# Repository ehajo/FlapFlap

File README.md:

# FlapFlap

Die Daten zum Fallblattanzeigen-Projekt, das wir auf Youtube und im Twitch-Livestream bearbeiten.

Unsere Streams findest du auf https://www.twitch.tv/ehajo

Die neue Version bekommt eine komplett neue Hardware. Es wird sowohl die komplette Ansteuerung als auch die Absolutpositionsabfrage getauscht!

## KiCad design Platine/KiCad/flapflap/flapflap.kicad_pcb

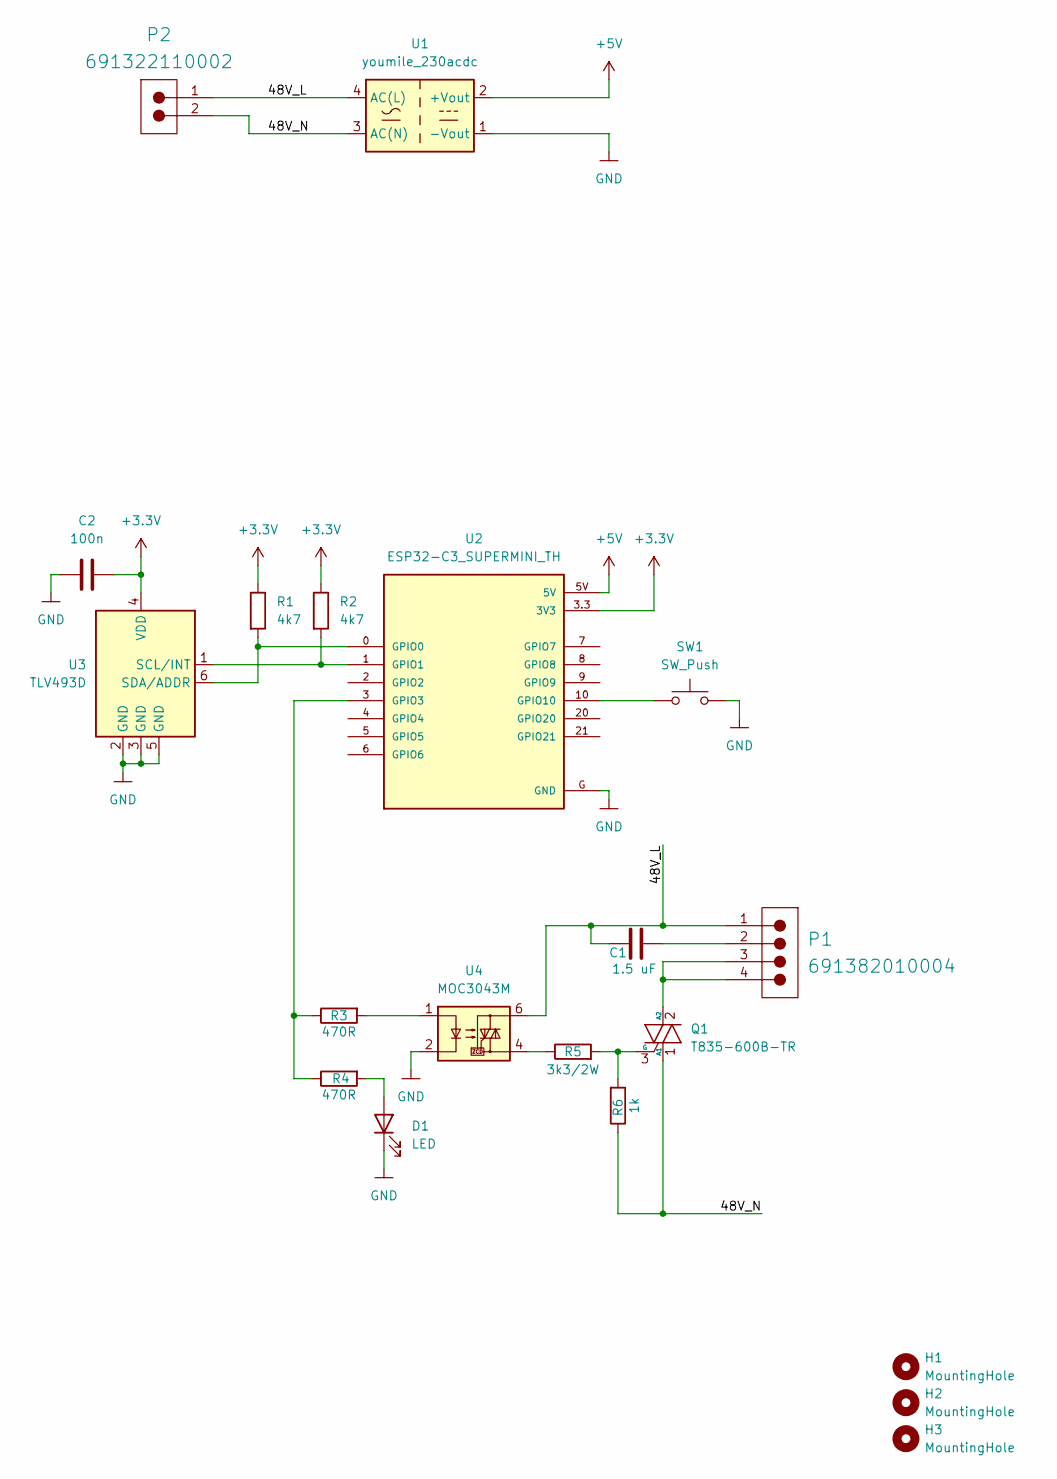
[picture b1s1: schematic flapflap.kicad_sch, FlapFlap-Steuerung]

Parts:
C1: 1.5 uF; C_Wurth_WCAP-FTBP-P22.5L26W7H16.5; Voltage 250; Part Number 890273326007CS
C2: 100n; C_0805_2012Metric_Pad1.18x1.45mm_HandSolder
D1: LED; LED_0805_2012Metric_Pad1.15x1.40mm_HandSolder
H1, H2, H3: MountingHole; MountingHole_3.2mm_M3
P1: 691382010004; 691382000004; Working Voltage 300V; Manufacturer Part Number 691382000004
P2: 691322110002; 691321300002; Working Voltage 300V; Manufacturer Part Number 691321300002
Q1: T835-600B-TR; TO-252-2
R1, R2: 4k7; R_0805_2012Metric_Pad1.20x1.40mm_HandSolder
R3, R4: 470R; R_0805_2012Metric_Pad1.20x1.40mm_HandSolder
R5: 3k3/2W; R_Axial_DIN0414_L11.9mm_D4.5mm_P15.24mm_Horizontal
R6: 1k; R_0805_2012Metric_Pad1.20x1.40mm_HandSolder
SW1: SW_Push; SW_SPST_FSMSM
U1: youmile_230acdc; ACDC-230
U2: ESP32-C3_SUPERMINI_TH; MODULE_ESP32-C3_SUPERMINI_TH
U3: TLV493D; SOT-23-6
U4: MOC3043M; DIP-6_W7.62mm_SMDSocket_SmallPads

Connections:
+3.3V: C2.2, R1.1, R2.1, U2.3.3 (3V3), U3.4 (VDD)
+5V: U1.2 (+Vout), U2.5V
/48V_L: C1.1, P1.1, P2.1, U1.4 (AC(L)), U4.6
/48V_N: P2.2, Q1.1 (A1), R6.1, U1.3 (AC(N))
GND: C2.1, D1.1 (K), SW1.1, U1.1 (-Vout), U2.G (GND), U3.2 (GND), U3.3 (GND), U3.5 (GND), U4.2
unnamed: C1.2, P1.2
unnamed: D1.2 (A), R4.2
unnamed: P1.3, P1.4, Q1.2 (A2)
unnamed: Q1.3 (G), R5.2, R6.2
unnamed: R3.2, U4.1
unnamed: R5.1, U4.4
unnamed: R1.2, U2.0 (GPIO0), U3.6 (SDA/ADDR)
unnamed: R2.2, U2.1 (GPIO1), U3.1 (SCL/INT)
unnamed: R3.1, R4.1, U2.3 (GPIO3)
unnamed: SW1.2, U2.10 (GPIO10)

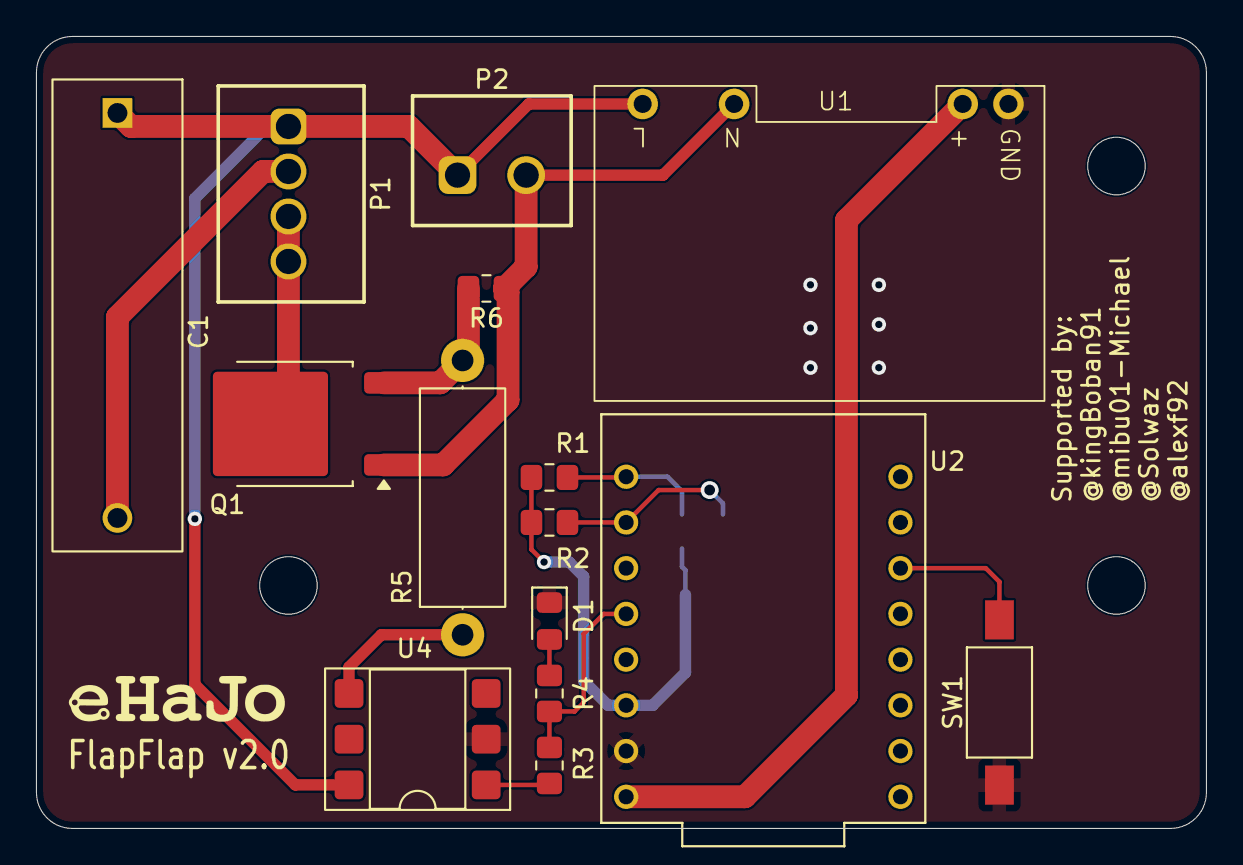
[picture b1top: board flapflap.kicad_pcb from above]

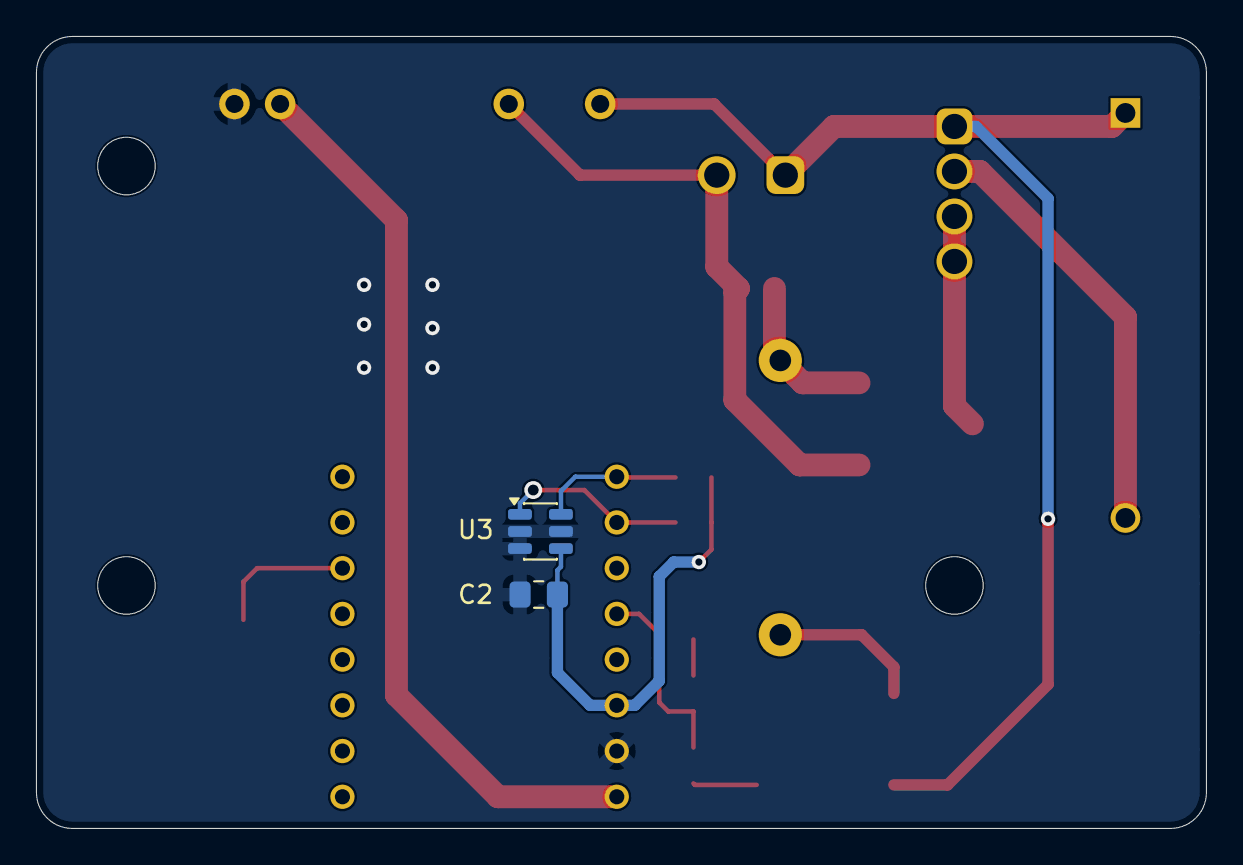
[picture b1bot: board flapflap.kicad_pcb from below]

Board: 2 copper layers, 65.0 x 44.0 mm, 20 parts (2 on the bottom side), 15 nets.

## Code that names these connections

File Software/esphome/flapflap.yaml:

esphome:
  name: flapflap-stunde
  on_boot:
    priority: -100
    then:
      - delay: 1s
      - lambda: |-
          id(tlv_test).set_pages((int) id(pages_number).state);
          id(tlv_test).set_zero_angle(id(zero_angle_number).state);
          id(tlv_test).set_calibration_leaf((int) id(calibration_leaf_number).state);
          id(tlv_test).set_target_leaf((int) id(target_leaf_number).state);
          id(tlv_test).set_mode("Stunden");

external_components:
  - source:
      type: local
      path: my_components

esp32:
  board: esp32-c3-devkitm-1
  framework:
    type: arduino

logger:
  level: DEBUG

api:
  encryption:
    key: "VgD8k05glNhFwXwStnMPbjwfET4pIDJ3TDBhezexu5A="

ota:
  - platform: esphome
    password: "1b5f8b66616918112e6f7647a8effe6e"

wifi:
  ssid: !secret wifi_ssid
  password: !secret wifi_password
  output_power: 8.5dB

time:
  - platform: sntp
    id: internet_time
    timezone: Europe/Berlin

i2c:
  sda: GPIO0
  scl: GPIO1
  scan: true
  frequency: 100kHz

binary_sensor:
  - platform: gpio
    id: flap_button
    name: "FlapFlap Taster"
    pin:
      number: GPIO10
      mode:
        input: true
        pullup: true
      inverted: true
    filters:
      - delayed_on: 20ms
      - delayed_off: 20ms
    on_press:
      then:
        - lambda: |-
            id(tlv_test).pulse_once();

button:
  - platform: restart
    name: "FlapFlap Neustart"

  - platform: template
    name: "FlapFlap Hier kalibrieren"
    on_press:
      then:
        - lambda: |-
            id(tlv_test).calibrate_here();
            auto call = id(zero_angle_number).make_call();
            call.set_value(id(tlv_test).get_zero_angle());
            call.perform();

  - platform: template
    name: "FlapFlap Sensor neu initialisieren"
    on_press:
      then:
        - lambda: |-
            id(tlv_test).reinitialize_sensor();

  - platform: template
    name: "FlapFlap Einzelpuls"
    on_press:
      then:
        - lambda: |-
            id(tlv_test).pulse_once();

  - platform: template
    name: "FlapFlap Ein Blatt weiter"
    on_press:
      then:
        - lambda: |-
            id(tlv_test).advance_one_leaf();

  - platform: template
    name: "FlapFlap Zu Zielblatt fahren"
    on_press:
      then:
        - lambda: |-
            id(tlv_test).start_move_to_target();

  - platform: template
    name: "FlapFlap Stop"
    on_press:
      then:
        - lambda: |-
            id(tlv_test).stop_move();

number:
  - platform: template
    name: "FlapFlap Nullwinkel"
    id: zero_angle_number
    min_value: 0
    max_value: 359.9
    step: 0.1
    optimistic: true
    restore_value: true
    initial_value: 0.0
    set_action:
      - lambda: |-
          id(tlv_test).set_zero_angle(x);

  - platform: template
    name: "FlapFlap Kalibrierblatt"
    id: calibration_leaf_number
    min_value: 0
    max_value: 61
    step: 1
    optimistic: true
    restore_value: true
    initial_value: 0
    set_action:
      - lambda: |-
          id(tlv_test).set_calibration_leaf((int) x);

  - platform: template
    name: "FlapFlap Zielblatt"
    id: target_leaf_number
    min_value: 0
    max_value: 61
    step: 1
    optimistic: true
    restore_value: true
    initial_value: 0
    set_action:
      - lambda: |-
          id(tlv_test).set_target_leaf((int) x);

  - platform: template
    name: "FlapFlap Blattanzahl"
    id: pages_number
    min_value: 1
    max_value: 100
    step: 1
    optimistic: true
    restore_value: true
    initial_value: 62
    set_action:
      - lambda: |-
          id(tlv_test).set_pages((int) x);

select:
  - platform: template
    name: "FlapFlap Modus"
    id: mode_select
    optimistic: true
    restore_value: false
    options:
      - Sekunden
      - Minuten
      - Stunden
      - Leerblatt
      - Kalibrierung
      - Manuell
    initial_option: Stunden
    set_action:
      - lambda: |-
          id(tlv_test).set_mode(x);

tlv493d_test:
  id: tlv_test
  update_interval: 20ms
  zero_angle: 0.0
  calibration_leaf: 0
  target_leaf: 0
  pages: 62
  mode: "Stunden"
  sensor_samples: 8
  motor_pin: GPIO3
  motor_pulse_ms: 30
  motor_settle_ms: 35
  move_timeout_ms: 15000
  max_pulses_per_move: 120
  unchanged_limit: 8
  move_stop_lead: 0.35
  seconds_stop_lead: 0.12

sensor:
  - platform: template
    name: "FlapFlap X"
    unit_of_measurement: "uT"
    accuracy_decimals: 1
    update_interval: 500ms
    lambda: |-
      return id(tlv_test).get_x_ut();

  - platform: template
    name: "FlapFlap Y"
    unit_of_measurement: "uT"
    accuracy_decimals: 1
    update_interval: 500ms
    lambda: |-
      return id(tlv_test).get_y_ut();

  - platform: template
    name: "FlapFlap Z"
    unit_of_measurement: "uT"
    accuracy_decimals: 1
    update_interval: 500ms
    lambda: |-
      return id(tlv_test).get_z_ut();

  - platform: template
    name: "FlapFlap Winkel"
    unit_of_measurement: "°"
    accuracy_decimals: 1
    update_interval: 500ms
    lambda: |-
      return id(tlv_test).get_angle_deg();

  - platform: template
    name: "FlapFlap Aktuelles Blatt"
    accuracy_decimals: 0
    update_interval: 250ms
    lambda: |-
      return id(tlv_test).get_current_leaf();

  - platform: template
    name: "FlapFlap Zielblatt aktiv"
    accuracy_decimals: 0
    update_interval: 250ms
    lambda: |-
      return id(tlv_test).get_target_leaf();

  - platform: template
    name: "FlapFlap Aktiver Nullwinkel"
    unit_of_measurement: "°"
    accuracy_decimals: 1
    update_interval: 1s
    lambda: |-
      return id(tlv_test).get_zero_angle();

  - platform: template
    name: "FlapFlap Pulse im aktuellen Lauf"
    accuracy_decimals: 0
    update_interval: 250ms
    lambda: |-
      return id(tlv_test).get_move_pulses();

text_sensor:
  - platform: template
    name: "FlapFlap Status"
    update_interval: 250ms
    lambda: |-
      return {id(tlv_test).get_status_text()};

interval:
  - interval: 1s
    then:
      - lambda: |-
          auto now = id(internet_time).now();
          if (now.is_valid()) {
            id(tlv_test).update_clock_time(now.hour, now.minute, now.second);
          }

  - interval: 10s
    then:
      - lambda: |-
          ESP_LOGD("main", "FlapFlap aktiv: I2C GPIO0/1, Taster GPIO10, MOC GPIO3");

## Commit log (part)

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2018-03-20 :boom::camel: Added .gitattributes & .gitignore files
2018-03-20 Initial commit
    Erste Version
2024-09-28 Sortiert in neuen Ordner
    Weg frei für die neue Version!
2024-10-02 CAD update
    jetzt sogar mit den richtigen Löchern und etwas größeren Löchern, damit man die M3 Schrauben sogar anschrauben kann!!
2024-10-02 rename
2024-10-02 Update Stream 1.10.24
    Non-Working version!
    Update im Stream, mit Winkelnullkalibrierung, Stufeneinteilung und noch Fehlern
2024-10-02 updated comment
    Wichtiges Kommentar zur Erklärung des Codes vergessen!
2024-10-03 initial commit
    addes libraries from ladyada to project
2024-10-03 initial commit
    our new config.json file for saving the zero-angle and step-target
2024-10-03 stream 2.10.24
    - added config.json support for destination-step and for zero-point calibration
    - flapflap until destination reached
    - some changes to sensor value aquisition
2024-10-09 Anpassungen an PCB
    Öffnung vergrößert, damit man jetzt auch eine Platine in das Gehäuse schrauben kann. Davor war es ja für Jumeprwires ausgelegt
2024-10-09 added pulsonix backup
    Ordner 001-Pulsonix ist für Backups da, der muss jetzt ned unbedingt ins Git...
2024-10-09 Initial commit
    erste, noch nichtmal ansatzweise fertige Version der Platine
2024-10-09 angepasst an die platine die rein kommt.
    jetzt mit anschlag für die platine, damit der sensor perfekt liegt
2024-10-09 finale
    platine fertig geroutet, ganz schön viel angepasst. RPi auf die Unterseite, RTC und so mit auf einen I2C, pins ausgeblendet vom rpi etc
2024-10-09 initial commit
    ganz viele CAD-Daten wegen Step-Datei von der Platine
2024-10-09 Initial commit
    Fertigungsdaten für die Platine als Gerber und in Zip
2024-10-10 optimierung
    fase an der bohrung weggelassen, macht nur probleme beim 3d-druck und ich habe eh keine passenden senkkopfschrauben hier...
2024-10-10 small changes
    nur stp neu exportiert und 3d druckdaten aktualisiert
2024-10-10 Anpassungen light
    Step ohne Fase und am Rand die Ausnehmung wieder hinzu, wurde unabsichtlich wegoptimiert
2024-10-16 Stream 15.10.24
    Aktualisierte Version vom Stream. Wir fragen jetzt die Zeit ab und wandeln Sommer/Winterzeit um. Kleine Änderungen nach dem Stream: Hauptschleife optimiert für mehr Stabilität
2024-10-16 Optimierungen
    Loch für Welle etwas verkleinert. Muss im Zweifel aufgebohrt werden, soll aber halt einfach gscheid passen...
2024-10-16 step aktualisiert
    step datei mit den neuen cad-daten exportiert
2024-10-16 optimierung
    kleine optimierungen damit der code besser läuft für den nächsten stream
2024-10-23 Minor changes
    Kleine Anpassungen bei der Nullpunktkalibrierung... Ersten Wert verwerfen und dann Average von 10 nehmen zwecks Genauigkeit und so
2024-10-23 Streamupdate
    Diesmal mit richtig rum gepolten Triac, aber noch nicht fertitsch....
2024-10-24 Platinenupdate
    Fehler ausgebessert, Widerstand vergrößert (2W) für Triac-Ansteuerung. Triac jetzt richtig belegt. Wenn es immer noch nicht geht: Chat ist Schuld!
2024-10-24 Stundenanzeige
    Jetzt auch für Stunden-FlapFlap umprogrammiert
2024-11-05 minor changes
    changed from pages to type now
2024-11-05 maincloc-subclock erste schritte
    code angepasst, um subclocks via serial zu ermöglichen. to be tested
2024-11-05 inital commi
    first try für subclock
2024-11-07 moved to subfolder
2024-11-07 initial commit
    subfolder for subclock with code.py. optimized and seems working atm
2024-11-07 minor
2024-11-07 updated serial communication
    now with 3 bytes to send. every subclock get every data and act as configured in config.json.
2024-11-08 initial commit
    schnelles gehäuse 3d-gedruckt, damit die 230V verstaut sind und sich nur wenige leute damit umbringen können.
2024-11-11 update with KI
    ChatGPT hat uns eine Anleitung geschrieben, toll, oder?
2024-11-11 Minor changes
    Ein paar Kleinigkeiten ausgebessert, die ChatGPT verbockt hat
2024-11-11 First final Version
    Finalisierte Version vom Livestream vom 11.11. (keine Faschingsversion, funktioniert echt!)
2024-11-18 initial commit
    PDF vom Schaltplan
2025-08-20 newest version
    now with webinterface and hightech zeuch
2026-04-06 komplett überarbeitet
2026-04-06 kingB's v1
